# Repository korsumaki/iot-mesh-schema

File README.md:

# iot-mesh-schema
Schematics and PCB for IoT sensor device

## Description

This PCB is used to connect Meshtastic Node with Wemos d1 mini arduino.

Temperature and humidity/pressure sensors are connected to Wemos.

Firmware for Wemos is  [arduino-iot-sensors](https://github.com/korsumaki/arduino-iot-sensors) repository.

## Board

## Schematics

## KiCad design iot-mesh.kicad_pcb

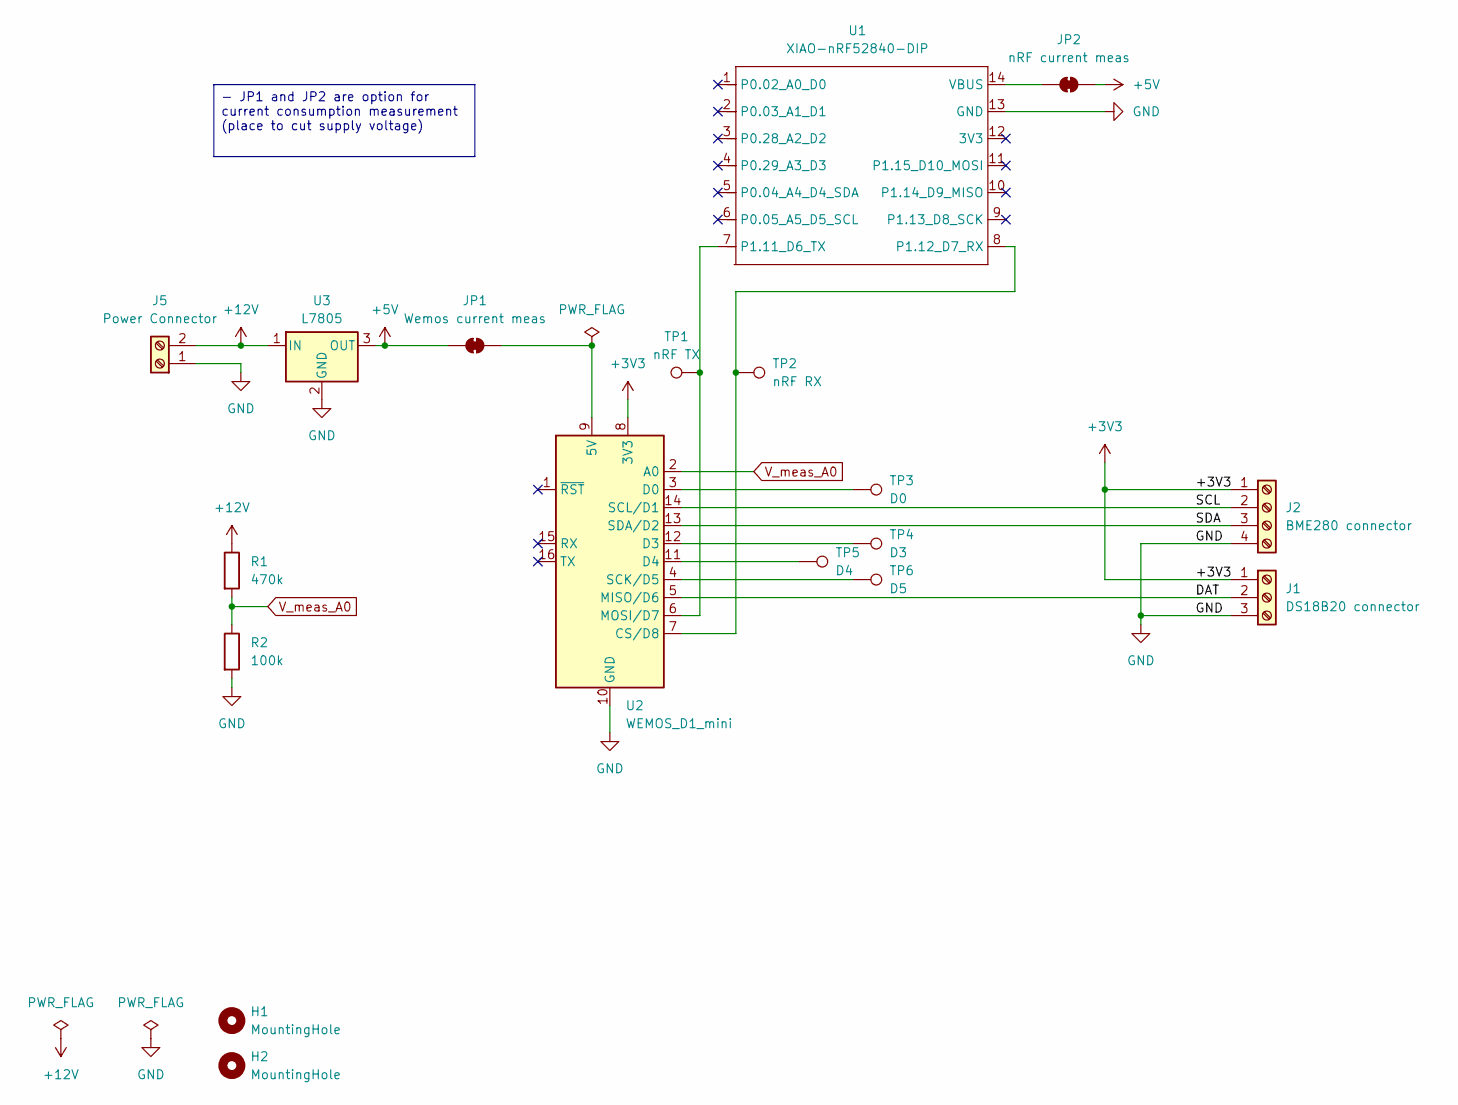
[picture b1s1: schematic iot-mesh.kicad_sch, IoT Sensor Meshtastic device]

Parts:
H1, H2: MountingHole; MountingHole_3.2mm_M3
J1: DS18B20 connector; TerminalBlock_Phoenix_PT-1,5-3-3.5-H_1x03_P3.50mm_Horizontal
J2: BME280 connector; TerminalBlock_Phoenix_PT-1,5-4-3.5-H_1x04_P3.50mm_Horizontal
J5: Power Connector; TerminalBlock_Phoenix_PT-1,5-2-3.5-H_1x02_P3.50mm_Horizontal
JP1: Wemos current meas; SolderJumper-2_P1.3mm_Bridged_RoundedPad1.0x1.5mm
JP2: nRF current meas; SolderJumper-2_P1.3mm_Bridged_RoundedPad1.0x1.5mm
R1: 470k; R_Axial_DIN0207_L6.3mm_D2.5mm_P10.16mm_Horizontal
R2: 100k; R_Axial_DIN0207_L6.3mm_D2.5mm_P10.16mm_Horizontal
TP1: nRF TX; TestPoint_Pad_D2.0mm
TP2: nRF RX; TestPoint_Pad_D2.0mm
TP3: D0; TestPoint_Pad_D2.0mm
TP4: D3; TestPoint_Pad_D2.0mm
TP5: D4; TestPoint_Pad_D2.0mm
TP6: D5; TestPoint_Pad_D2.0mm
U1: XIAO-nRF52840-DIP; XIAO-nRF52840-DIP-mk
U2: WEMOS_D1_mini; WEMOS_D1_mini_light
U3: L7805; TO-220-3_Vertical

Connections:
+3V3: J1.1, J2.1, U2.8 (3V3)
+5V: JP1.2 (B), JP2.2 (B), U3.3 (OUT)
+12V: J5.2, R1.1, U3.1 (IN)
/DAT: J1.2, U2.5 (MISO/D6)
/SCL: J2.2, U2.14 (SCL/D1)
/SDA: J2.3, U2.13 (SDA/D2)
GND: J1.3, J2.4, J5.1, R2.2, U1.13 (GND), U2.10 (GND), U3.2 (GND)
unnamed: JP1.1 (A), U2.9 (5V)
unnamed: JP2.1 (A), U1.14 (VBUS)
unnamed: TP1.1, U1.7 (P1.11_D6_TX), U2.6 (MOSI/D7)
unnamed: TP2.1, U1.8 (P1.12_D7_RX), U2.7 (CS/D8)
unnamed: TP3.1, U2.3 (D0)
unnamed: TP4.1, U2.12 (D3)
unnamed: TP5.1, U2.11 (D4)
unnamed: TP6.1, U2.4 (SCK/D5)
V_meas_A0: R1.2, R2.1, U2.2 (A0)

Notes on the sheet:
- JP1 and JP2 are option for current consumption measurement (place to cut supply voltage)

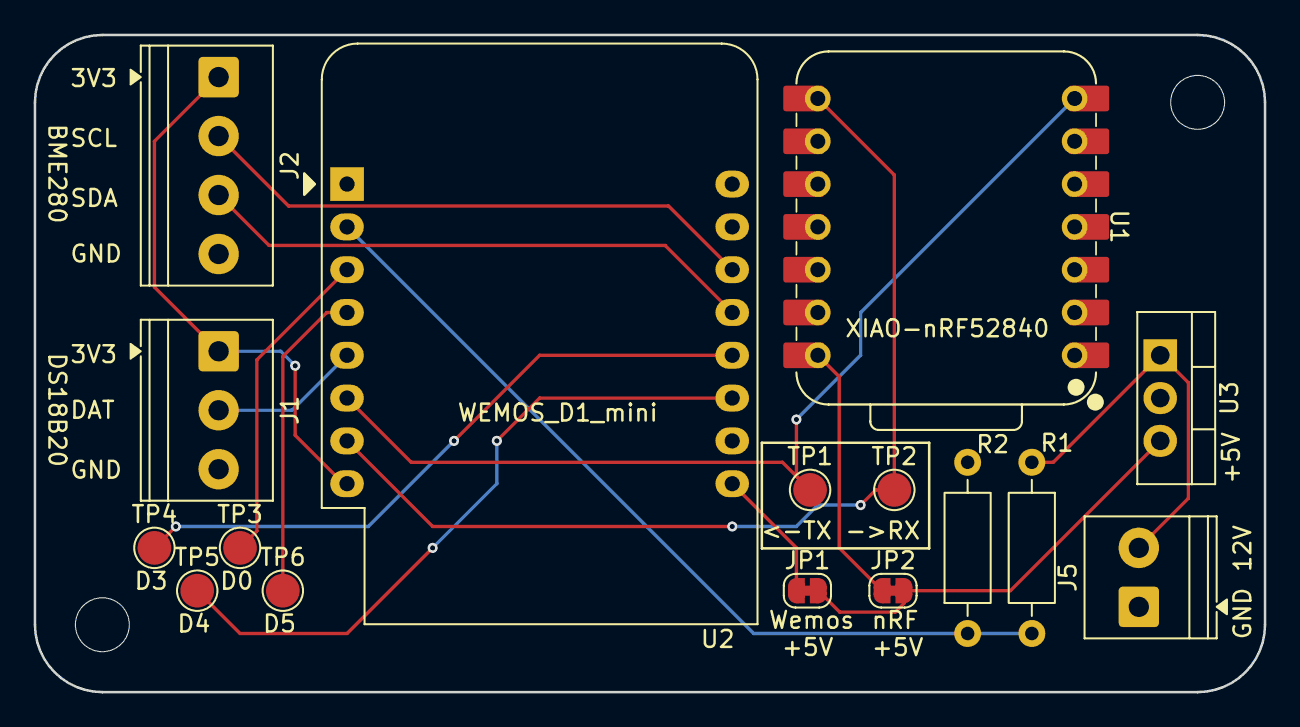
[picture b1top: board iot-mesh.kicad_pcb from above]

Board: 2 copper layers, 73.0 x 39.0 mm, 18 parts (0 on the bottom side), 16 nets.

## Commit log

2026-03-03 First schematics and PCB version
2026-03-03 Add pin headers for nRF
2026-03-04 Test way to select components
2026-03-04 Update schematics
2026-03-05 Add project specific symbol and footprint
    XIAO-nRF52840-DIP is modified so that silkscreen does not go over pads.
2026-03-05 Update title block
2026-03-05 Line width changes on silkscreen and edges
2026-03-09 Component selections and updates for preparing order
2026-03-11 Update README.md, add images
